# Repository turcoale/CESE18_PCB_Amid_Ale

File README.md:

# CESE18_PCB_Amid_Ale
Trabajo final de la asignatura Diseño de PCB de la CESE

** Principales Características:**

1. Salidas a Relay (2)
2. Entradas Optoacopladas (4)
3. (RS232)Conector Biométrico (1)
4. (RS232) ESP8266 (1)
5. Display 16x2 (1)
6. (SPI) Módulo conector sensor RFID

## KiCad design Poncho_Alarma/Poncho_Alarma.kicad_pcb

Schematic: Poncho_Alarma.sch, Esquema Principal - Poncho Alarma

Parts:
DS1: LCD16X2; WC1602A
J1: ESP8266; PinHeader_2x04_P2.54mm_Vertical
R1: 10K; TRIMER_V
XA1: Conn_Poncho2P_2x_20x2; poncho_grande

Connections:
+5V: DS1.2, R1.1, XA1.2; also elsewhere on the board
/Entradas/In_1: XA1.76; also elsewhere on the board
/Entradas/In_2: XA1.78; also elsewhere on the board
/Entradas/In_3: XA1.80; also elsewhere on the board
/Entradas/In_4: XA1.74; also elsewhere on the board
/Salidas/Out_1: XA1.69; also elsewhere on the board
/Salidas/Out_2: XA1.71; also elsewhere on the board
GND: DS1.1, DS1.5, J1.1, J1.5, R1.3; also elsewhere on the board
unnamed: DS1.3, R1.2
unnamed: DS1.4, XA1.64
unnamed: DS1.6, XA1.63
unnamed: DS1.11, XA1.70
unnamed: DS1.12, XA1.68
unnamed: DS1.13, XA1.66
unnamed: DS1.14, XA1.62
unnamed: J1.2, XA1.23
unnamed: J1.7, XA1.25

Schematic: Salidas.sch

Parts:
D1, D2: LED_Rojo; LED_D3.0mm
D3, D4: LL4148; D_DO-201AD_P12.70mm_Horizontal
J2: Salidas; TerminalBlock_bornier-6_P5.08mm
K1, K2: RELAY_C; Relay_C
Q1, Q2: 2N7002; SOT23
R2, R3: 100k; R_Axial_DIN0204_L3.6mm_D1.6mm_P5.08mm_Horizontal
R4, R5: 330; R_Axial_DIN0204_L3.6mm_D1.6mm_P5.08mm_Horizontal

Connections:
+5V: D1.2 (A), D2.2 (A), D3.1 (K), D4.1 (K), K1.5, K2.5; also elsewhere on the board
/Salidas/K1_C: J2.2, K1.1
/Salidas/K1_NA: J2.1, K1.3
/Salidas/K1_NC: J2.3, K1.4
/Salidas/K2_C: J2.5, K2.1
/Salidas/K2_NA: J2.4, K2.3
/Salidas/K2_NC: J2.6, K2.4
/Salidas/Out_1: Q1.1 (G), R2.1; also elsewhere on the board
/Salidas/Out_2: Q2.1 (G), R3.1; also elsewhere on the board
GND: Q1.2 (S), Q2.2 (S), R2.2, R3.2; also elsewhere on the board
unnamed: D1.1 (K), R4.1
unnamed: D2.1 (K), R5.1
unnamed: D3.2 (A), K1.2, Q1.3 (D), R4.2
unnamed: D4.2 (A), K2.2, Q2.3 (D), R5.2

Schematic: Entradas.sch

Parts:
D5, D6, D7, D8: LED_Rojo; LED_D3.0mm
J3: Entradas; TerminalBlock_bornier-4_P5.08mm
R6, R7, R8, R9: R_Small3.3K; R_Axial_DIN0204_L3.6mm_D1.6mm_P5.08mm_Horizontal
R10, R11, R12, R13: 4.7K; R_Axial_DIN0204_L3.6mm_D1.6mm_P5.08mm_Horizontal
R14, R16, R18, R20: 2.2K; R_Axial_DIN0204_L3.6mm_D1.6mm_P5.08mm_Horizontal
R15, R17, R19, R21: 100K; R_Axial_DIN0204_L3.6mm_D1.6mm_P5.08mm_Horizontal
U1: TLP627-4; DIP-16_W7.62mm

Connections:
/Entradas/In_1: R7.1; also elsewhere on the board
/Entradas/In_2: R8.1; also elsewhere on the board
/Entradas/In_3: R9.1; also elsewhere on the board
/Entradas/In_4: R6.1; also elsewhere on the board
GND: R10.1, R11.1, R12.1, R13.1, U1.2, U1.4, U1.6, U1.8, U1.9, U1.11, U1.13, U1.15; also elsewhere on the board
unnamed: D5.1 (K), J3.4, R15.2, U1.16
unnamed: D5.2 (A), R14.2
unnamed: D6.1 (K), J3.1, R17.2, U1.14
unnamed: D6.2 (A), R16.2
unnamed: D7.1 (K), J3.2, R19.2, U1.12
unnamed: D7.2 (A), R18.2
unnamed: D8.1 (K), J3.3, R21.2, U1.10
unnamed: D8.2 (A), R20.2
unnamed: R6.2, R10.2, U1.1
unnamed: R7.2, R11.2, U1.3
unnamed: R8.2, R12.2, U1.5
unnamed: R9.2, R13.2, U1.7

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
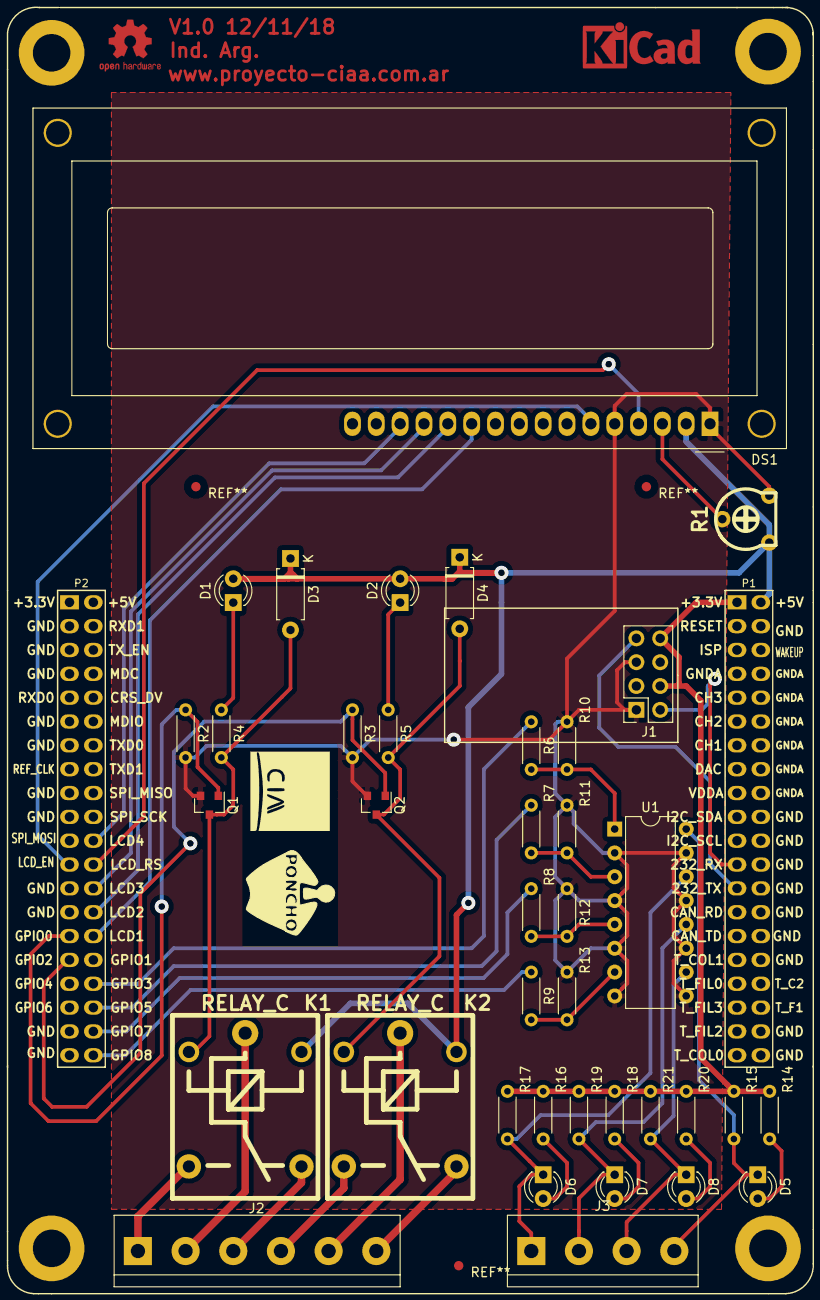
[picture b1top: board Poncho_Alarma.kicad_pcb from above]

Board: 2 copper layers, 41 parts (0 on the bottom side), 40 nets.

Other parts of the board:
G102: LOGO_CIAA; LOGO-CIAA
MP1: Plantilla_EDU-CIAA

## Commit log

2018-09-14 Creada carpeta documentación
2018-09-14 crecion del proyecto
2018-09-14 editando el Readme
2018-10-22 trabajando en el esquemático
2018-10-27 Esquematico Terminado
2018-10-30 asociando componentes
2018-10-30 arreglado lo de la libreria
2018-10-30 Posicionado terminado
2018-10-31 Terminado ruteado
2018-11-05 mascara cobre
2018-11-12 Correcciónes
2018-11-12 Agregando Relays 3D
2018-11-12 fiduciales e inscripciones
2018-11-12 rellenando zonas de cobre
